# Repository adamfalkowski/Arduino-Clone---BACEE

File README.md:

# Arduino-Clone---BACEE
PCB Design - Arduino Clone 

https://help.github.com/en/github/importing-your-projects-to-github/adding-an-existing-project-to-github-using-the-command-line

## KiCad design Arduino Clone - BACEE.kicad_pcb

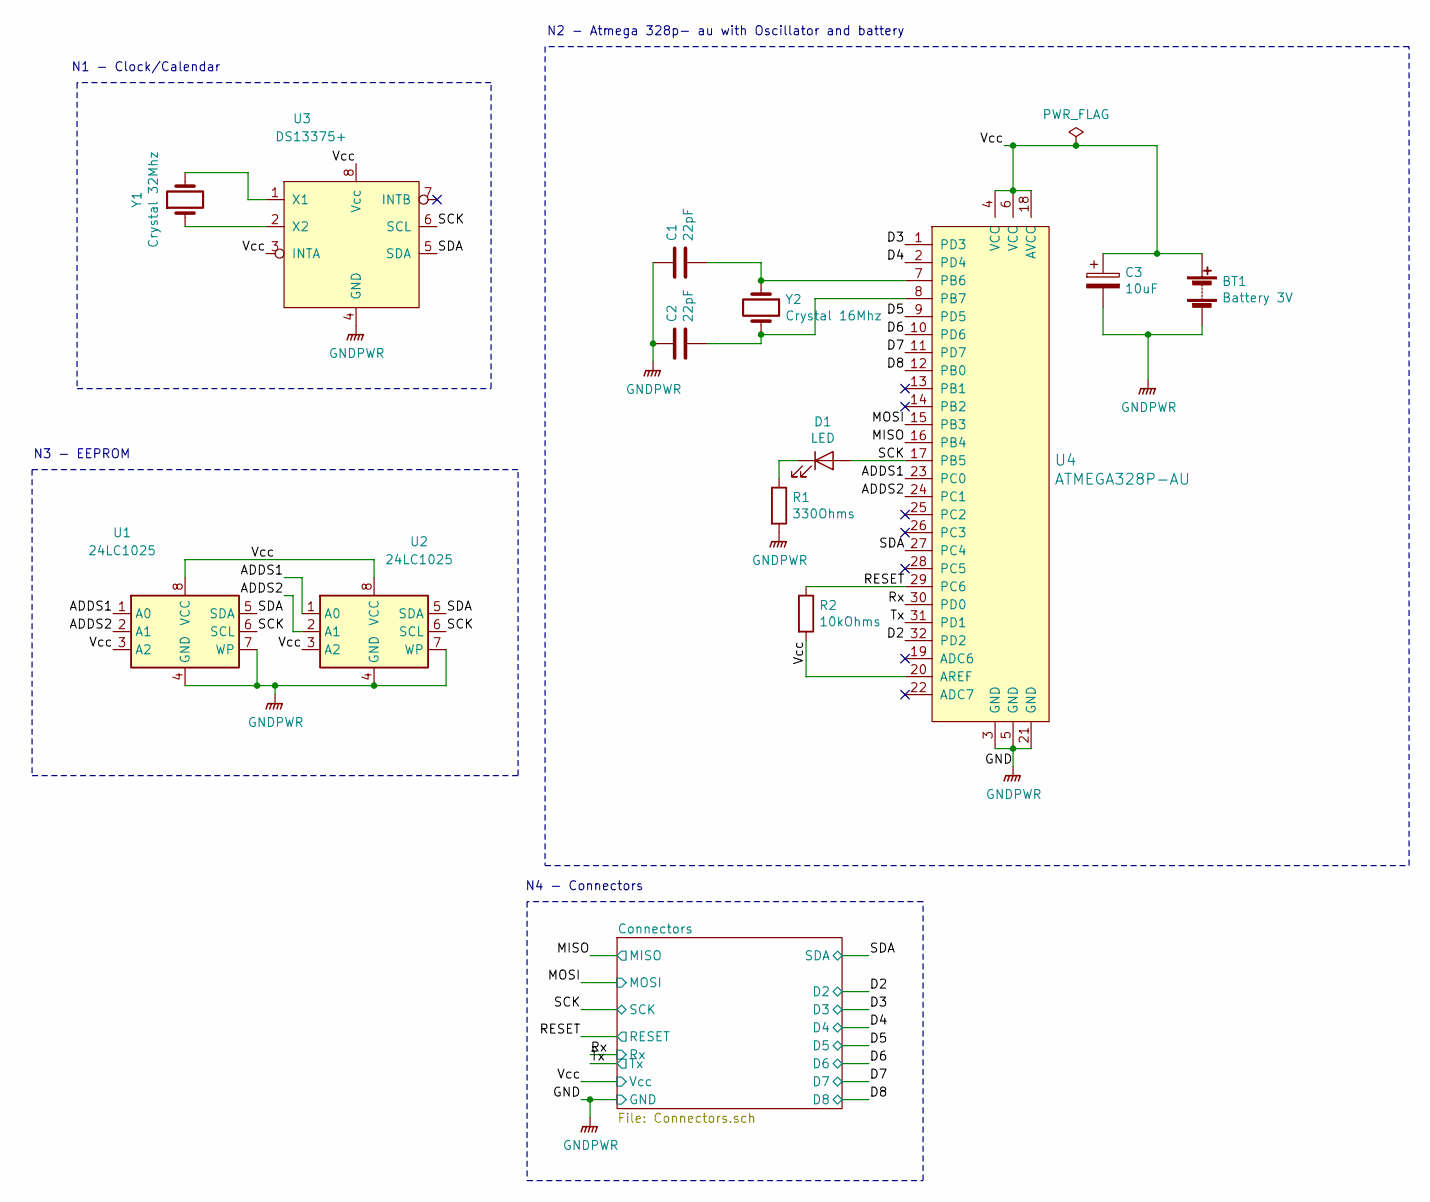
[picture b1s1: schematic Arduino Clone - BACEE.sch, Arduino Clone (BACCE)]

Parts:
BT1: Battery 3V; PinHeader_1x02_P2.54mm_Vertical
C1, C2: 22pF; C_0805_2012Metric_Pad1.15x1.40mm_HandSolder
C3: 10uF; C_0805_2012Metric_Pad1.15x1.40mm_HandSolder
D1: LED; LED_0805_2012Metric_Pad1.15x1.40mm_HandSolder
R1: 330Ohms; R_0805_2012Metric_Pad1.15x1.40mm_HandSolder
R2: 10kOhms; R_0805_2012Metric_Pad1.15x1.40mm_HandSolder
U1, U2: 24LC1025; SOIJ-8_5.3x5.3mm_P1.27mm
U3: DS13375+; SO-8_5.3x6.2mm_P1.27mm
U4: ATMEGA328P-AU; TQFP-32_7x7mm; MPN ATMEGA328P-AU; Digi-Key_PN ATMEGA328P-AU-ND
Y1: Crystal 32Mhz; Crystal_SMD_MicroCrystal_CC7V-T1A-2Pin_3.2x1.5mm
Y2: Crystal 16Mhz; Crystal_SMD_5032-2Pin_5.0x3.2mm_HandSoldering

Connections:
/ADDS1: U1.1 (A0), U2.1 (A0), U4.23 (PC0)
/ADDS2: U1.2 (A1), U2.2 (A1), U4.24 (PC1)
/D2: U4.32 (PD2); also elsewhere on the board
/D3: U4.1 (PD3); also elsewhere on the board
/D4: U4.2 (PD4); also elsewhere on the board
/D5: U4.9 (PD5); also elsewhere on the board
/D6: U4.10 (PD6); also elsewhere on the board
/D7: U4.11 (PD7); also elsewhere on the board
/D8: U4.12 (PB0); also elsewhere on the board
/MISO: U4.16 (PB4); also elsewhere on the board
/MOSI: U4.15 (PB3); also elsewhere on the board
/RESET: R2.1, U4.29 (PC6); also elsewhere on the board
/Rx: U4.30 (PD0); also elsewhere on the board
/SCK: D1.2 (A), U1.6 (SCL), U2.6 (SCL), U3.6 (SCL), U4.17 (PB5); also elsewhere on the board
/SDA: U1.5 (SDA), U2.5 (SDA), U3.5 (SDA), U4.27 (PC4); also elsewhere on the board
/Tx: U4.31 (PD1); also elsewhere on the board
/Vcc: BT1.1 (+), C3.1, R2.2, U1.3 (A2), U1.8 (VCC), U2.3 (A2), U2.8 (VCC), U3.3 (INTA), U3.8 (Vcc), U4.4 (VCC), U4.6 (VCC), U4.18 (AVCC), U4.20 (AREF); also elsewhere on the board
GNDPWR: BT1.2 (-), C1.1, C2.1, C3.2, R1.2, U1.4 (GND), U1.7 (WP), U2.4 (GND), U2.7 (WP), U3.4 (GND), U4.3 (GND), U4.5 (GND), U4.21 (GND); also elsewhere on the board
unnamed: C1.2, U4.7 (PB6), Y2.1
unnamed: C2.2, U4.8 (PB7), Y2.2
unnamed: D1.1 (K), R1.1
unnamed: U3.1 (X1), Y1.2
unnamed: U3.2 (X2), Y1.1

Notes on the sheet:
N1 - Clock/Calendar
N2 - Atmega 328p- au with Oscillator and battery
N3 - EEPROM
N4 - Connectors

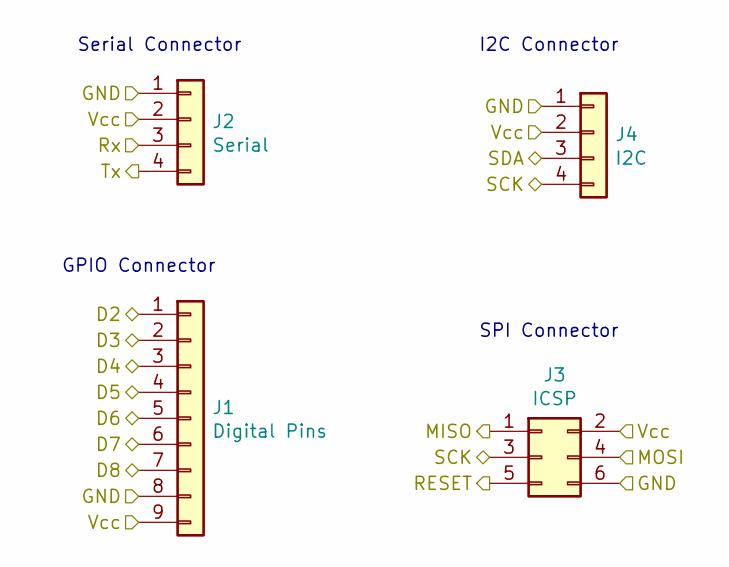
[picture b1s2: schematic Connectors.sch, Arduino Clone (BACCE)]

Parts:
J1: Digital Pins; PinSocket_1x09_P2.54mm_Vertical
J2: Serial; PinSocket_1x04_P2.54mm_Vertical
J3: ICSP; PinSocket_2x03_P2.54mm_Vertical
J4: I2C; PinSocket_1x04_P2.54mm_Vertical

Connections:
/D2: J1.1; also elsewhere on the board
/D3: J1.2; also elsewhere on the board
/D4: J1.3; also elsewhere on the board
/D5: J1.4; also elsewhere on the board
/D6: J1.5; also elsewhere on the board
/D7: J1.6; also elsewhere on the board
/D8: J1.7; also elsewhere on the board
/MISO: J3.1; also elsewhere on the board
/MOSI: J3.4; also elsewhere on the board
/RESET: J3.5; also elsewhere on the board
/Rx: J2.3; also elsewhere on the board
/SCK: J3.3, J4.4; also elsewhere on the board
/SDA: J4.3; also elsewhere on the board
/Tx: J2.4; also elsewhere on the board
/Vcc: J1.9, J2.2, J3.2, J4.2; also elsewhere on the board
GNDPWR: J1.8, J2.1, J3.6, J4.1; also elsewhere on the board

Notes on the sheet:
Serial Connector
I2C Connector
GPIO Connector
SPI Connector

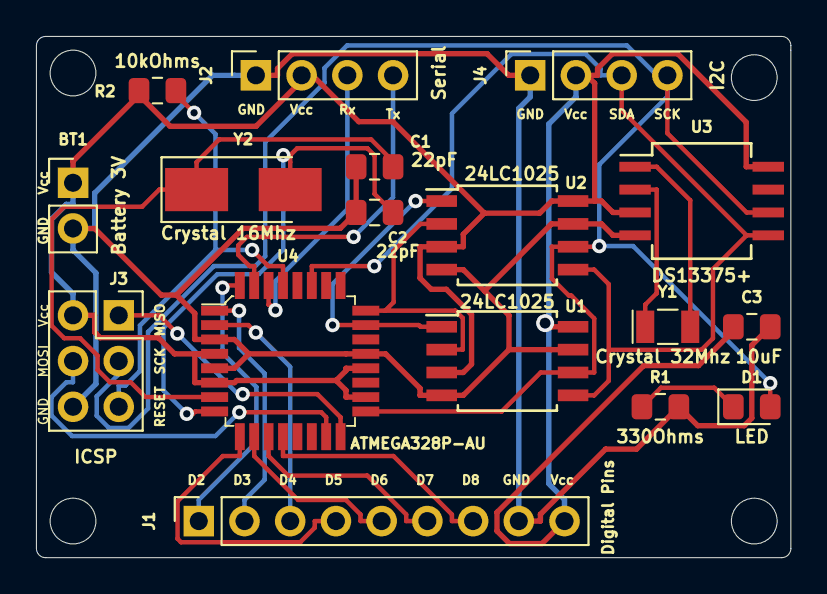
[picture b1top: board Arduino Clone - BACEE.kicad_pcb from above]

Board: 2 copper layers, 41.9 x 29.0 mm, 17 parts (0 on the bottom side), 23 nets.

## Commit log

2020-04-05 Setup the title block in schematic sheet
2020-04-05 Created new child sheet, added proj symbols
2020-04-05 Added symbol for atmega328p-au
2020-04-05 Added clock IC custom
2020-04-06 Added missing crystal
2020-04-06 symbol rearrangement
2020-04-06 Annotate
2020-04-06 associations
2020-04-06 Completed wiring in connectors
2020-04-07 wiring
2020-04-07 Comments
2020-04-07 Gen Netlist
2020-04-07 Started work in PCB new
2020-04-07 Set Design Rules
2020-04-07 Placement
2020-04-07 2 layer autorouted
2020-04-07 Copper Fields - 2 layers
2020-04-07 silkscreens
